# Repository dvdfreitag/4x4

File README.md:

# 4x4
A 4x4 mechanical keyboard

More or less a clone of https://github.com/di0ib/Misc/tree/master/4x4, but with a different controller. An Arduino Pro Micro instead of an Arduino Micro, they're much easier to get.

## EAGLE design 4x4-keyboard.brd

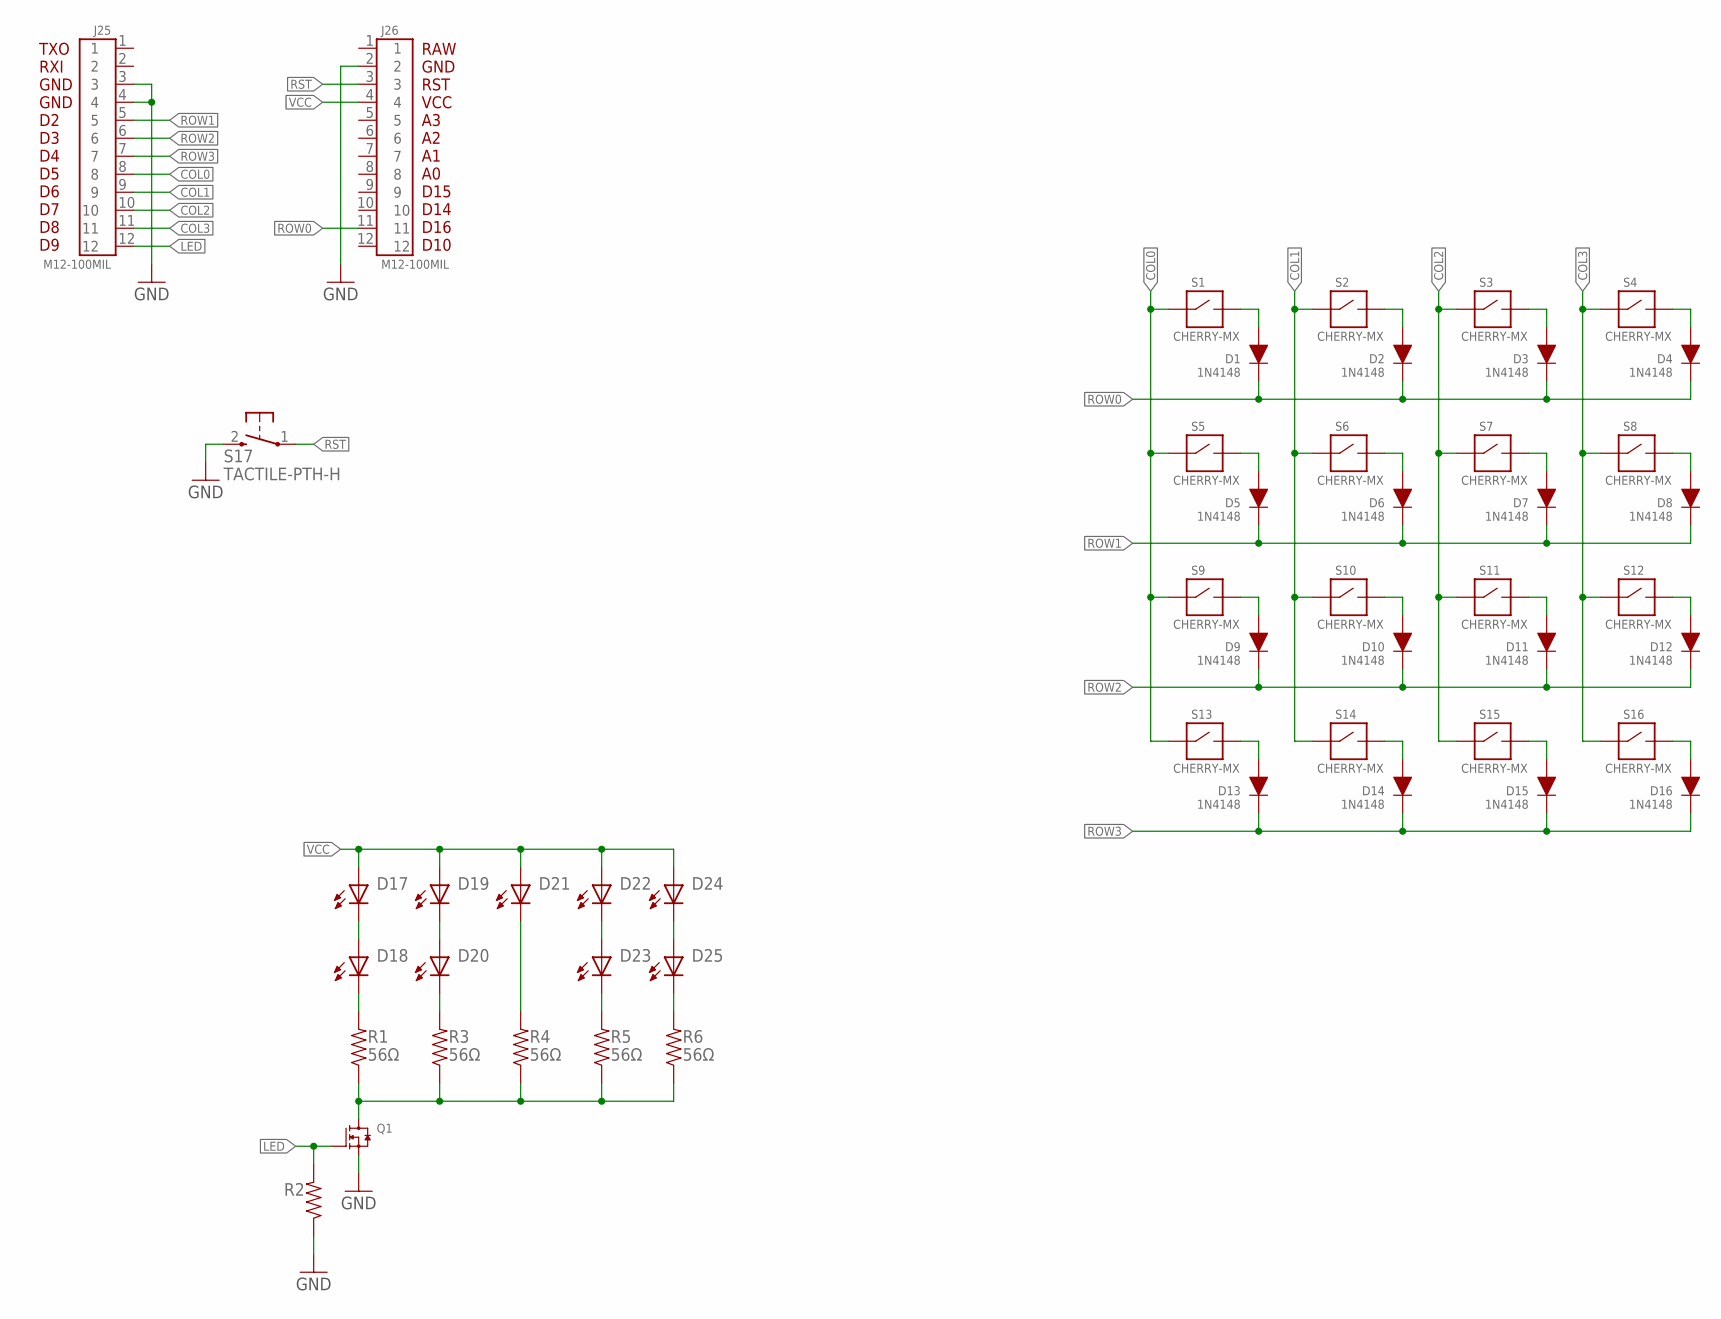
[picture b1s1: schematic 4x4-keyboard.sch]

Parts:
D1, D2, D3, D4, D5, D6, D7, D8, D9, D10, D11, D12, D13, D14, D15, D16: 1N4148; DIODE-PTH
D17, D18, D19, D20, D21, D22, D23, D24, D25: LED-3MM; 3MM-LED
J25, J26: M12-100MIL; M12X1
Q1: N-MOSFET-TO-92; TO-92-3
R1, R3, R4, R5, R6: 56Ω; RESISTOR-PTH
R2: RESISTOR-PTH
S1, S2, S3, S4, S5, S6, S7, S8, S9, S10, S11, S12, S13, S14, S15, S16: CHERRY-MX
S17: TACTILE-PTH-H; TACTILE-HORIZONTAL

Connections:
COL0: J25.8, S1.S1, S1.S4 (S1), S5.S1, S5.S4 (S1), S9.S1, S9.S4 (S1), S13.S1, S13.S4 (S1)
COL1: J25.9, S2.S1, S2.S4 (S1), S6.S1, S6.S4 (S1), S10.S1, S10.S4 (S1), S14.S1, S14.S4 (S1)
COL2: J25.10, S3.S1, S3.S4 (S1), S7.S1, S7.S4 (S1), S11.S1, S11.S4 (S1), S15.S1, S15.S4 (S1)
COL3: J25.11, S4.S1, S4.S4 (S1), S8.S1, S8.S4 (S1), S12.S1, S12.S4 (S1), S16.S1, S16.S4 (S1)
GND: J25.3, J25.4, J26.2, Q1.1 (SOURCE), R2.P$1 (1), S17.2 (3)
LED: J25.12, Q1.2 (GATE), R2.P$2 (2)
unnamed: D3.A, S3.S2, S3.S3 (S2)
unnamed: D4.A, S4.S2, S4.S3 (S2)
unnamed: D2.A, S2.S2, S2.S3 (S2)
unnamed: D1.A, S1.S2, S1.S3 (S2)
unnamed: Q1.3 (DRAIN), R1.P$1 (1), R3.P$1 (1), R4.P$1 (1), R5.P$1 (1), R6.P$1 (1)
unnamed: D9.A, S9.S2, S9.S3 (S2)
unnamed: D10.A, S10.S2, S10.S3 (S2)
unnamed: D11.A, S11.S2, S11.S3 (S2)
unnamed: D12.A, S12.S2, S12.S3 (S2)
unnamed: D16.A, S16.S2, S16.S3 (S2)
unnamed: D15.A, S15.S2, S15.S3 (S2)
unnamed: D14.A, S14.S2, S14.S3 (S2)
unnamed: D13.A, S13.S2, S13.S3 (S2)
unnamed: D5.A, S5.S2, S5.S3 (S2)
unnamed: D6.A, S6.S2, S6.S3 (S2)
unnamed: D7.A, S7.S2, S7.S3 (S2)
unnamed: D8.A, S8.S2, S8.S3 (S2)
unnamed: D21.C, R4.P$2 (2)
unnamed: D24.C, D25.A
unnamed: D22.C, D23.A
unnamed: D23.C, R5.P$2 (2)
unnamed: D25.C, R6.P$2 (2)
unnamed: D19.C, D20.A
unnamed: D20.C, R3.P$2 (2)
unnamed: D18.C, R1.P$2 (2)
unnamed: D17.C, D18.A
ROW0: D1.C, D2.C, D3.C, D4.C, J26.11
ROW1: D5.C, D6.C, D7.C, D8.C, J25.5
ROW2: D9.C, D10.C, D11.C, D12.C, J25.6
ROW3: D13.C, D14.C, D15.C, D16.C, J25.7
RST: J26.3, S17.1
VCC: D17.A, D19.A, D21.A, D22.A, D24.A, J26.4

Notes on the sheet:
TXO RXI GND GND D2 D3 D4 D5 D6 D7 D8 D9
RAW GND RST VCC A3 A2 A1 A0 D15 D14 D16 D10

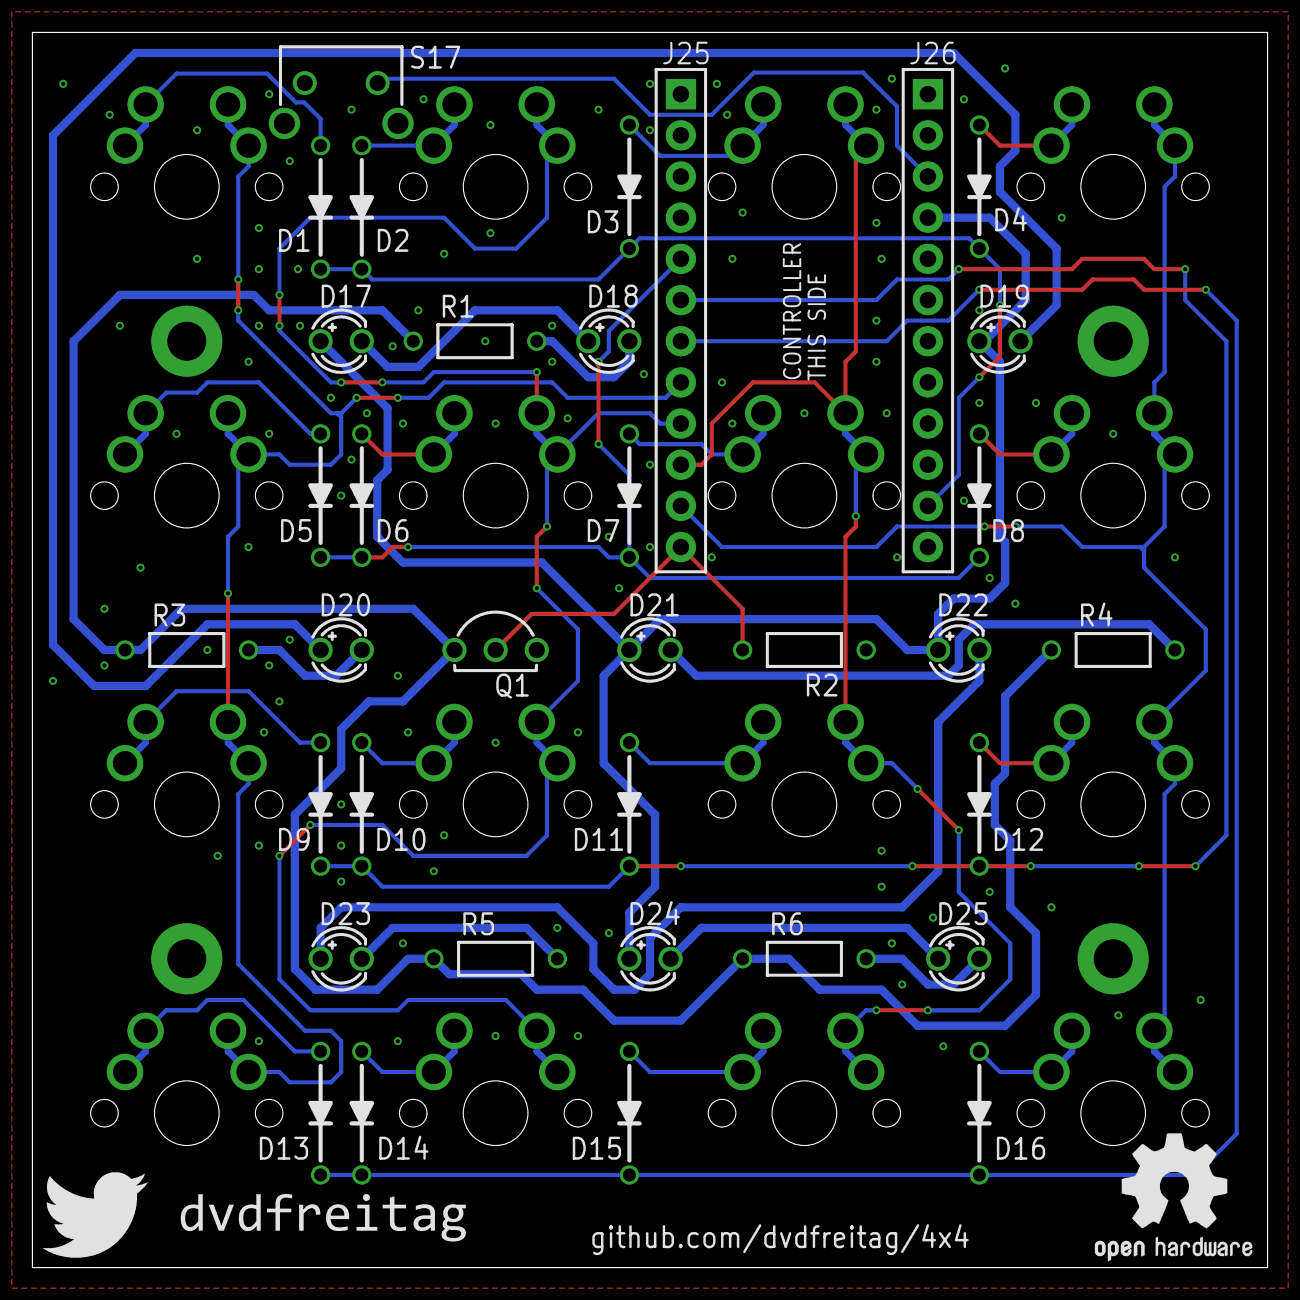
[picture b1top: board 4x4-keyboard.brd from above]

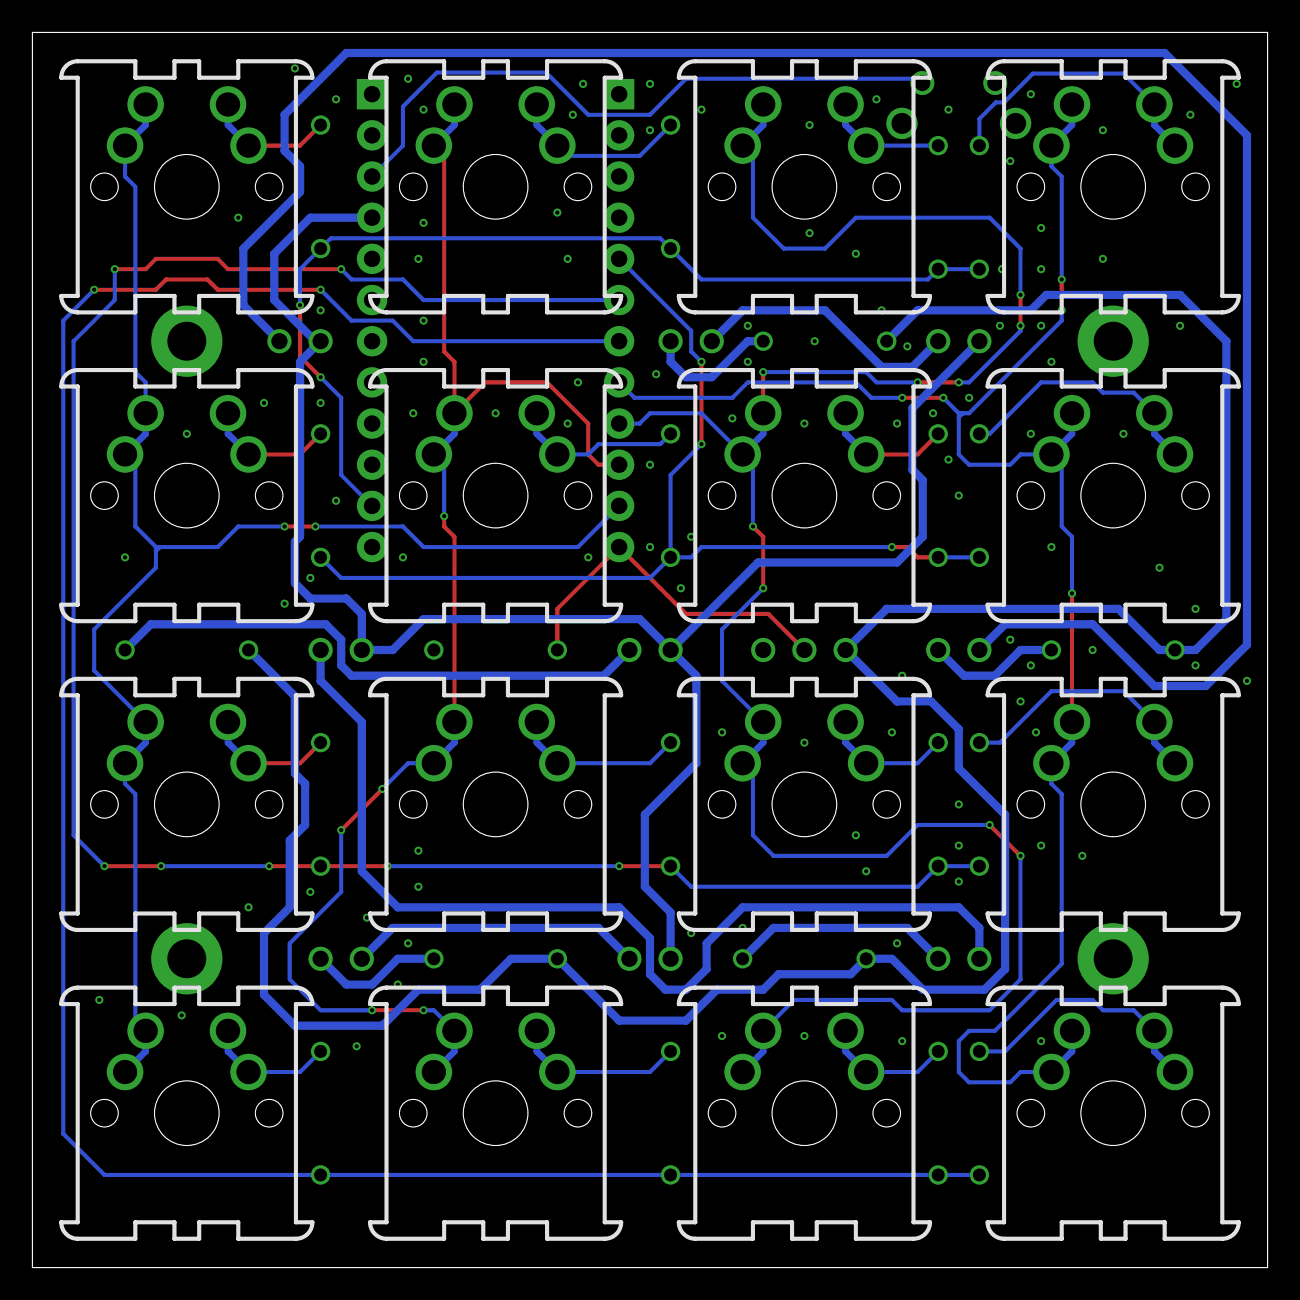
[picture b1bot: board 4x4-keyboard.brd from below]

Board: 2 copper layers, 76.2 x 76.2 mm, 53 parts (16 on the bottom side), 38 nets.

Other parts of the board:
U$1: TWITTER
U$2: OSHW

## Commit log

2018-06-23 Add drawings
    Add dimensional drawing and dxf for laser cutting
2018-07-06 Add json file
    The JSON file from the 40% 4x4 works fairly well, although I managed to
    mirror the columns. That is the only change in this file.
2018-11-14 Update layout
    - Remove extensible connectors
    - Add backlight 3mm leds instead of frontlight smd
    - Add I/O-controlled mosfet for driving dimmable backlight
    - Add reset switch
